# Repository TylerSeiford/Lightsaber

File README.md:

# Lightsaber
This is the kicad files and code for my custom lightsaber controller.

## Hardware
This uses an ATmega32u4 microcontroller to control addressable and non addressable LED strips, with a single button input.

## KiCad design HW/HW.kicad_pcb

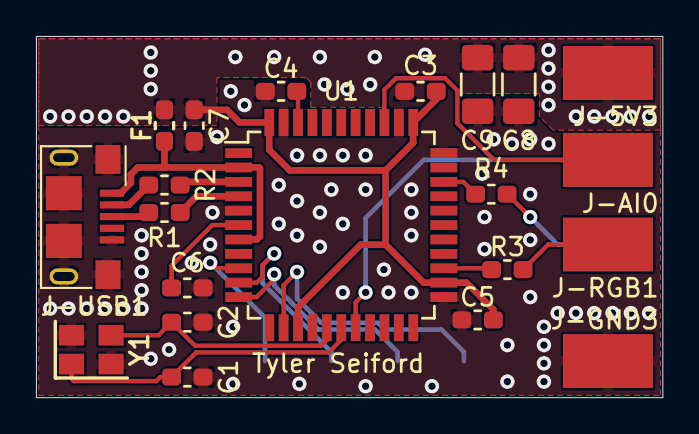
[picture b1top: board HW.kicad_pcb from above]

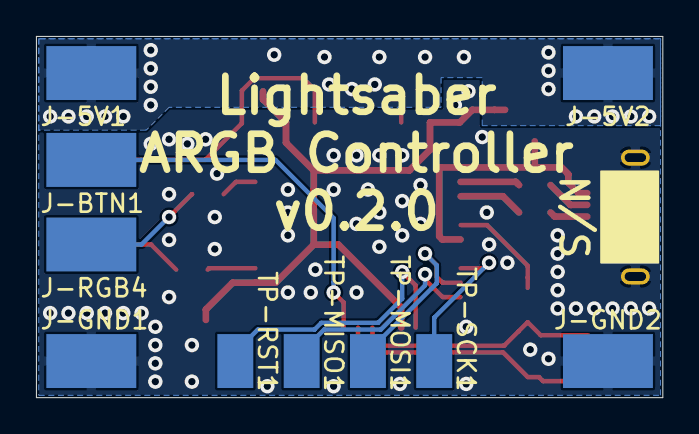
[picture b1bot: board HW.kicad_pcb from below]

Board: 2 copper layers, 34.8 x 20.1 mm, 31 parts (10 on the bottom side), 21 nets.

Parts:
C1, C2: 22pF; C_0603_1608Metric_Pad1.05x0.95mm_HandSolder
C3, C4: 0.1uF; C_0603_1608Metric_Pad1.05x0.95mm_HandSolder
C5, C6: 1uF; C_0603_1608Metric_Pad1.05x0.95mm_HandSolder
C7: 10uF; C_0603_1608Metric_Pad1.05x0.95mm_HandSolder
C8, C9: 100uF; C_1206_3216Metric_Pad1.42x1.75mm_HandSolder
F1: Polyfuse; Fuse_0603_1608Metric_Pad1.05x0.95mm_HandSolder
J-5V1, J-5V2, J-5V3: Conn_01x01_Female; SolderPad
J-AI0: Conn_01x01_Female; SolderPad
J-BTN1: Conn_01x01_Female; SolderPad
J-GND1, J-GND2, J-GND3: Conn_01x01_Female; SolderPad
J-RGB1, J-RGB4: Conn_01x01_Female; SolderPad
J-USB1: USB_B_Micro; USB_Micro-B
R1, R2: 22; R_0603_1608Metric_Pad1.05x0.95mm_HandSolder
R3, R4: 470ohm; R_0603_1608Metric_Pad1.05x0.95mm_HandSolder
TP-MISO1: TestPoint; Program-Pad
TP-MOSI1: TestPoint; Program-Pad
TP-RST1: TestPoint; Program-Pad
TP-SCK1: TestPoint; Program-Pad
U1: ATmega32U4-AU; TQFP-44_10x10mm_P0.8mm
Y1: Crystal_GND24; Crystal_SMD_SeikoEpson_TSX3225-4Pin_3.2x2.5mm

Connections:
/Microcontroller/AREF: C4.1, U1.42
/Microcontroller/D+: R1.1, U1.4
/Microcontroller/D+USB: J-USB1.3, R1.2
/Microcontroller/D-: R2.2, U1.3
/Microcontroller/D-USB: J-USB1.2, R2.1
/Microcontroller/RESET: TP-RST1.1, U1.13
/Microcontroller/UCAP: C6.1, U1.6
/Microcontroller/XTAL1: C1.1, U1.17, Y1.1
/Microcontroller/XTAL2: C2.1, U1.16, Y1.3
/RGB1: J-RGB1.1, R3.2
/RGB2: J-RGB4.1, R4.2
AI0: J-AI0.1, U1.36
AVCC: C3.2, C5.2, C7.1, C8.1, C9.1, F1.2, J-5V1.1, J-5V2.1, J-5V3.1, U1.14, U1.24, U1.34, U1.44
D3: J-BTN1.1, U1.18
D4: R3.1, U1.25
D5: R4.1, U1.31
D14: TP-MISO1.1, U1.11
D15: TP-SCK1.1, U1.9
D16: TP-MOSI1.1, U1.10
GND: C1.2, C2.2, C3.1, C4.2, C5.1, C6.2, C7.2, C8.2, C9.2, J-GND1.1, J-GND2.1, J-GND3.1, J-USB1.5, J-USB1.6, U1.5, U1.15, U1.23, U1.33, U1.35, U1.43, Y1.2, Y1.4
UVCC: F1.1, J-USB1.1, U1.2, U1.7

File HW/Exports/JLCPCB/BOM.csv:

Comment,Designator,Footprint,LCSC Part Number
ATmega32U4,U1,QFP-44_10x10x08P,C44854
16MHz Crystal,Y1,SMD-2520_4P,C284159
22pF 0603,"C1, C2",603,C1653
10uF 6.3V 0603,C7,603,C19702
100uF 6.3V 1206,"C8, C9",1206,C15008
22ohm 0603,"R1, R2",603,C23345
1uF 0603,"C5, C6",603,C15849
0.1uF 0603,"C3, C4",603,C14663
500mA 0603,F1,603,C261937
470ohm 0603,"R3, R4",603,C23179

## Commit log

2019-12-29 v0.0.1
2019-12-29 Removed addressable pin
2019-12-29 Added button pin, small cleanup
2019-12-30 Still need a regulator, but other than that it's done
2020-01-01 v0.0.2, still need a cap for the strip
2020-01-01 v0.0.5
2020-01-01 v0.0.6, ready to order!
2020-01-02 v0.1.0
    Ordered PCB
2020-01-11 Added exports
2020-01-11 Initial software upload
    This code switches between Blue, Green, Purple, Yellow and White saber colors.
2020-01-22 Added programming pads - WIP
2020-01-22 Working code with a toggle switchbutton
2020-01-24 Update to 60 led/m
2020-01-24 PCB v0.1.4
2020-01-25 v0.1.5
2020-01-25 Switch to 60 led/m
2020-01-25 Revert "Switch to 60 led/m"
    This reverts commit ea5cab5998039afd6ec0f1096afdc589358bb988.
2020-01-25 Revert "v0.1.5"
    This reverts commit e4fecfe9a0bde4f9dc583f5ceb0710b3b709af1d.
2020-01-26 Exports and v0.1.5
2020-01-26 File cleanup
2020-02-02 Small updates
2020-02-08 Move Exports
2020-02-11 v0.2.0
2020-03-04 Fixed some small issues
    Switched back to 60led/m, removed Yellow and White modes, and reduced brightness in Yellow and White modes.
